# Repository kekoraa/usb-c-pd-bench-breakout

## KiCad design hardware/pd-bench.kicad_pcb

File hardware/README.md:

# KiCad project

Open **pd-bench.kicad_pro** in KiCad 10.0.x. Revision 0.2 contains a fully routed PCB, checked with KiCad CLI 10.0.5. Keep this folder and its local libraries together.

```text
hardware/
  pd-bench.kicad_pro       Project settings and net classes
  pd-bench.kicad_sch       One-sheet A3 schematic (electrically unchanged)
  pd-bench.kicad_pcb       Routed 80 x 70 mm two-layer PCB
  pd-bench.kicad_dru       Documented J1-specific design rules
  sym-lib-table           Project-relative symbol library
  fp-lib-table            Project-relative footprint library
  libraries/
    PD_Bench.kicad_sym
    PD_Bench.pretty/
```

The PCB contains 27 schematic-linked footprints and four board-only mounting holes, 112 track segments, 48 vias and three filled copper zones. There are zero unconnected items under the supplied DRC. Four additional zones are mounting-hardware keepout areas, not copper pours.

Local symbols and footprints are derived from KiCad standard libraries. The MOSFET symbol represents G1/D2/S3. J3/J4 nominal drills have been changed to 1.1 mm in both board and local libraries. The USB footprint retains the manufacturer's land pattern and uses a documented 0.19 mm internal hole-clearance rule. Fabricator acceptance of its nominal 0.1944 mm spacing remains open.

Optional component 3D bodies reference KiCad's standard model library. The supplied bare-board CAD render intentionally does not establish an assembled hardware result. Use the copper exports and native PCB to inspect routing.

Before fabrication, review the [layout](../docs/pcb-layout.md), [routing assessment](../docs/routing-review.md) and [open issues](../docs/open-issues.md). This is an unbuilt design prototype; no manufacturing files are released.

Re-run from the repository root with `kicad-cli` on the path:

```sh
kicad-cli sch erc -o verification/erc.rpt hardware/pd-bench.kicad_sch
kicad-cli sch export netlist --format kicadxml -o verification/netlist.xml hardware/pd-bench.kicad_sch
kicad-cli pcb drc --refill-zones --save-board --schematic-parity --exit-code-violations -o verification/drc.rpt hardware/pd-bench.kicad_pcb
python verification/check_connectivity.py
```

The optional `verification/inspect_routed_board.py` uses KiCad's bundled Python/pcbnew module to compare every PCB pin with the exported schematic and report routing/zone statistics. File checks are not electrical simulation or physical validation.

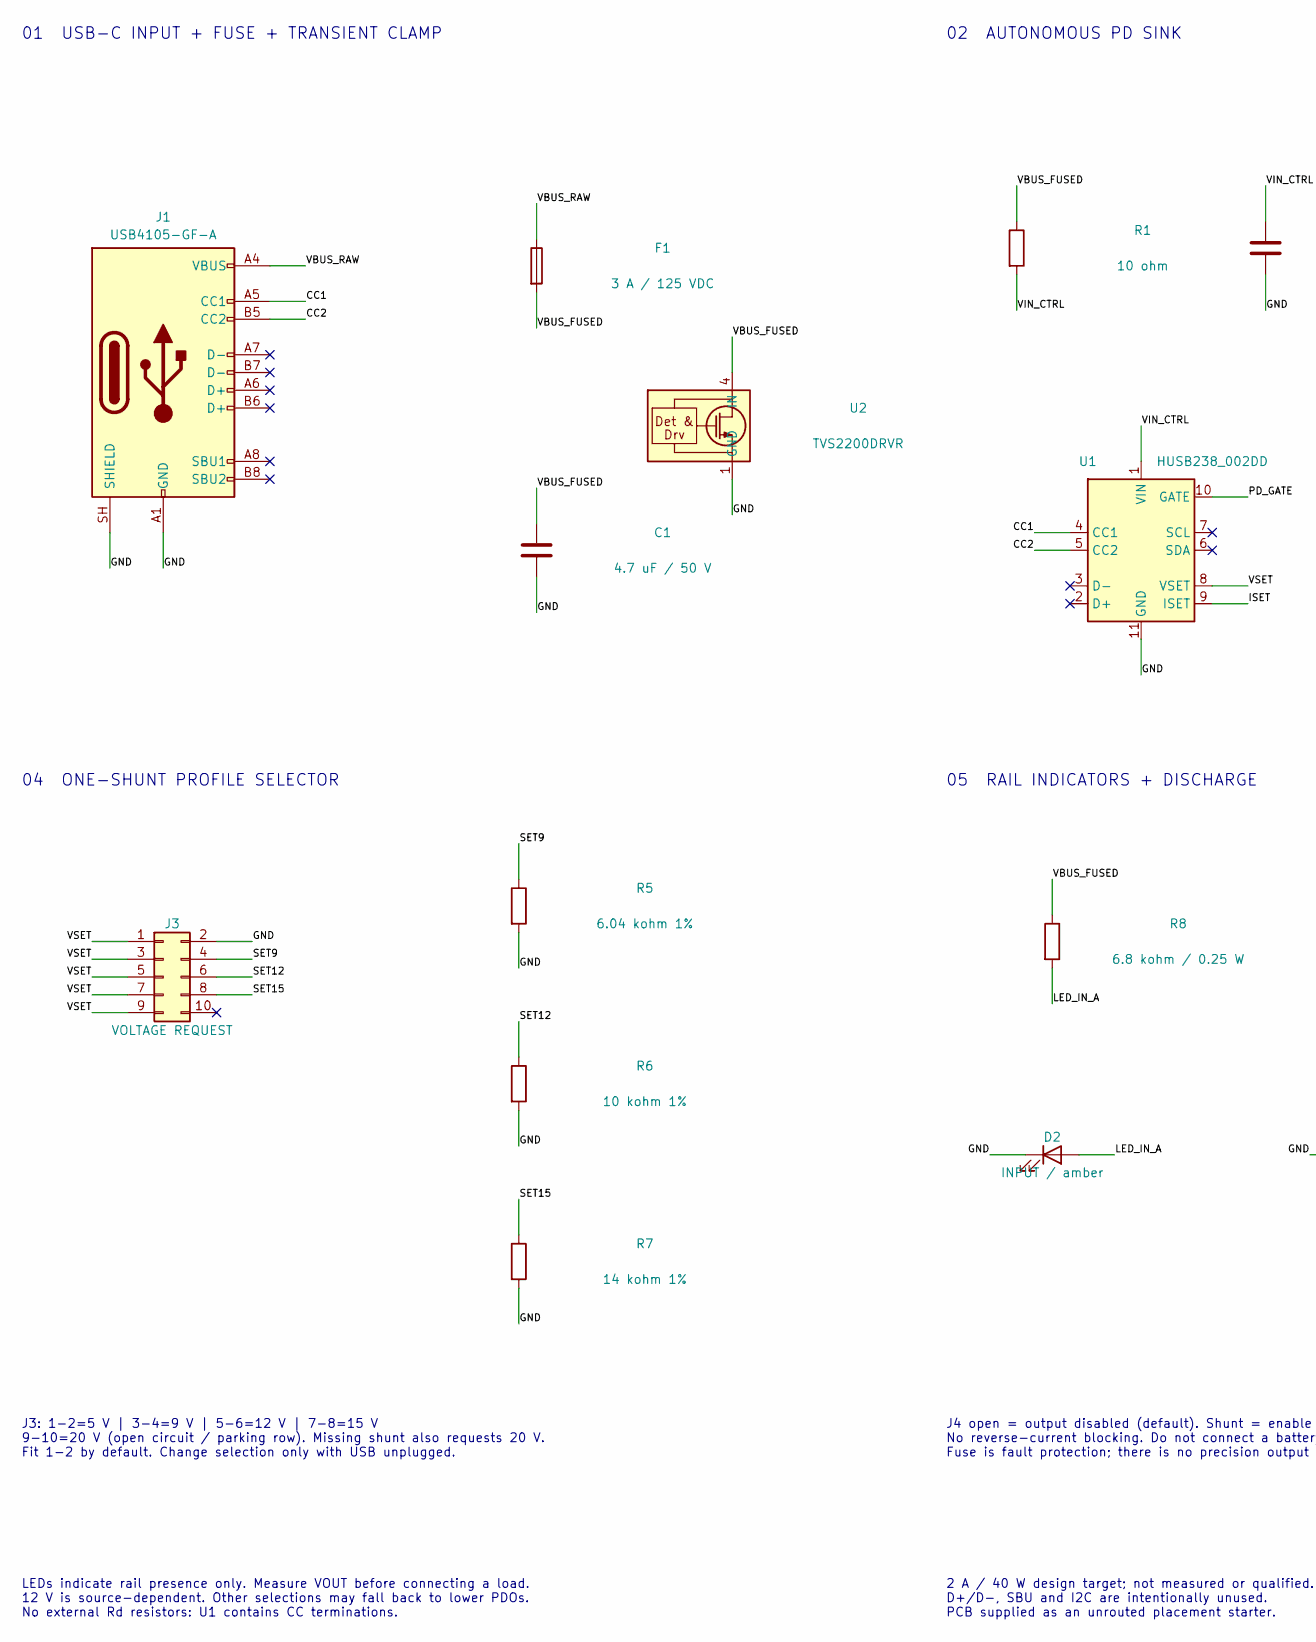
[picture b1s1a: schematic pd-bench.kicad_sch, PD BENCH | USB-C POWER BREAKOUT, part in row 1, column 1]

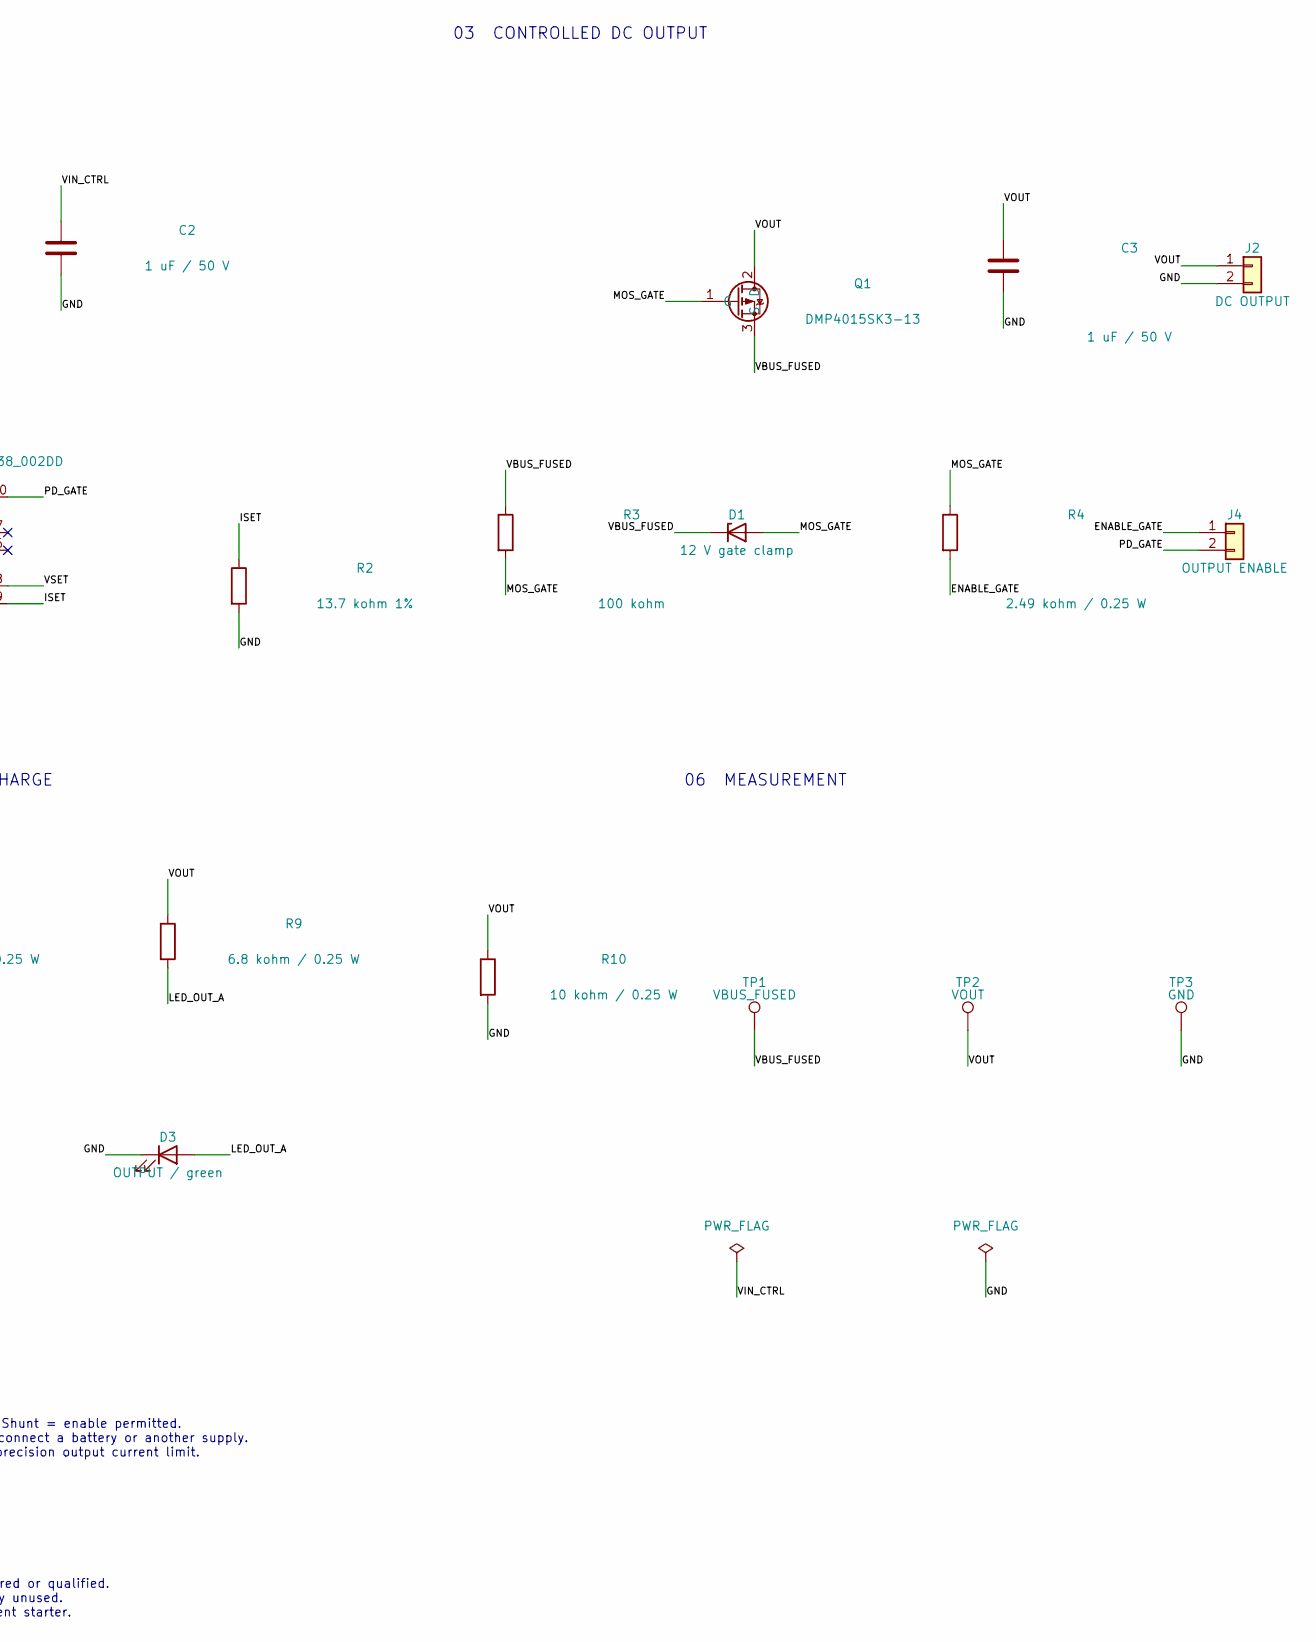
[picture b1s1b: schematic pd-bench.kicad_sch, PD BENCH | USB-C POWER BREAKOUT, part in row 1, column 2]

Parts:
C1: 4.7 uF / 50 V; C_1206_3216Metric; MPN GRM31CR71H475KA12L
C2, C3: 1 uF / 50 V; C_0805_2012Metric; MPN C2012X7R1H105K125AB
D1: 12 V gate clamp; D_SOD-123; MPN BZT52-C12X
D2: INPUT / amber; LED_0805_2012Metric; MPN LTST-C170KSKT
D3: OUTPUT / green; LED_0805_2012Metric; MPN LTST-C170KGKT
F1: 3 A / 125 VDC; Fuse_Littelfuse-NANO2-451_453; MPN 0451003.MRL
J1: USB4105-GF-A; USB_C_Receptacle_GCT_USB4105-xx-A_16P_TopMnt_Horizontal; MPN USB4105-GF-A
J2: DC OUTPUT; TerminalBlock_Phoenix_MKDS-1,5-2_1x02_P5.00mm_Horizontal; MPN 1715022
J3: VOLTAGE REQUEST; PinHeader_2x05_P2.54mm_Vertical; MPN 61301021121
J4: OUTPUT ENABLE; PinHeader_1x02_P2.54mm_Vertical; MPN 61300211121
Q1: DMP4015SK3-13; TO-252-2; MPN DMP4015SK3-13
R1: 10 ohm; R_0805_2012Metric; MPN RC0805FR-0710RL
R2: 13.7 kohm 1%; R_0805_2012Metric; MPN RC0805FR-0713K7L
R3: 100 kohm; R_0805_2012Metric; MPN RC0805FR-07100KL
R4: 2.49 kohm / 0.25 W; R_1206_3216Metric; MPN RC1206FR-072K49L
R5: 6.04 kohm 1%; R_0805_2012Metric; MPN RC0805FR-076K04L
R6: 10 kohm 1%; R_0805_2012Metric; MPN RC0805FR-0710KL
R7: 14 kohm 1%; R_0805_2012Metric; MPN RC0805FR-0714KL
R8, R9: 6.8 kohm / 0.25 W; R_1206_3216Metric; MPN RC1206FR-076K8L
R10: 10 kohm / 0.25 W; R_1206_3216Metric; MPN RC1206FR-0710KL
TP1: VBUS_FUSED; TestPoint_Pad_D2.0mm; MPN PCB pad
TP2: VOUT; TestPoint_Pad_D2.0mm; MPN PCB pad
TP3: GND; TestPoint_Pad_D2.0mm; MPN PCB pad
U1: HUSB238_002DD; WDFN-10-1EP_3x3mm_P0.5mm_EP1.8x2.5mm; MPN HUSB238_002DD
U2: TVS2200DRVR; WSON-6-1EP_2x2mm_P0.65mm_EP1x1.6mm; MPN TVS2200DRVR

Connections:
/CC1: J1.A5 (CC1), U1.4 (CC1)
/CC2: J1.B5 (CC2), U1.5 (CC2)
/ENABLE_GATE: J4.1, R4.2
/GND: C1.2, C2.2, C3.2, D2.1 (K), D3.1 (K), J1.A1 (GND), J1.A12 (GND), J1.B1 (GND), J1.B12 (GND), J1.SH (SHIELD), J2.2, J3.2, R2.2, R5.2, R6.2, R7.2, R10.2, TP3.1, U1.11 (GND), U2.1 (GND), U2.2 (GND), U2.3 (GND), U2.7 (GND)
/ISET: R2.1, U1.9 (ISET)
/LED_IN_A: D2.2 (A), R8.2
/LED_OUT_A: D3.2 (A), R9.2
/MOS_GATE: D1.2 (A), Q1.1 (G), R3.2, R4.1
/PD_GATE: J4.2, U1.10 (GATE)
/SET9: J3.4, R5.1
/SET12: J3.6, R6.1
/SET15: J3.8, R7.1
/VBUS_FUSED: C1.1, D1.1 (K), F1.2, Q1.3 (S), R1.1, R3.1, R8.1, TP1.1, U2.4 (IN), U2.5 (IN), U2.6 (IN)
/VBUS_RAW: F1.1, J1.A4 (VBUS), J1.A9 (VBUS), J1.B4 (VBUS), J1.B9 (VBUS)
/VIN_CTRL: C2.1, R1.2, U1.1 (VIN)
/VOUT: C3.1, J2.1, Q1.2 (D), R9.1, R10.1, TP2.1
/VSET: J3.1, J3.3, J3.5, J3.7, J3.9, U1.8 (VSET)

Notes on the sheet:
01 USB-C INPUT + FUSE + TRANSIENT CLAMP
02 AUTONOMOUS PD SINK
03 CONTROLLED DC OUTPUT
04 ONE-SHUNT PROFILE SELECTOR
05 RAIL INDICATORS + DISCHARGE
06 MEASUREMENT
J3: 1-2=5 V | 3-4=9 V | 5-6=12 V | 7-8=15 V 9-10=20 V (open circuit / parking row). Missing shunt also requests 20 V. Fit 1-2 by default. Change selection only with USB unplugged.
J4 open = output disabled (default). Shunt = enable permitted. No reverse-current blocking. Do not connect a battery or another supply. Fuse is fault protection; there is no precision output current limit.
LEDs indicate rail presence only. Measure VOUT before connecting a load. 12 V is source-dependent. Other selections may fall back to lower PDOs. No external Rd resistors: U1 contains CC terminations.
2 A / 40 W design target; not measured or qualified. D+/D-, SBU and I2C are intentionally unused. PCB supplied as an unrouted placement starter.

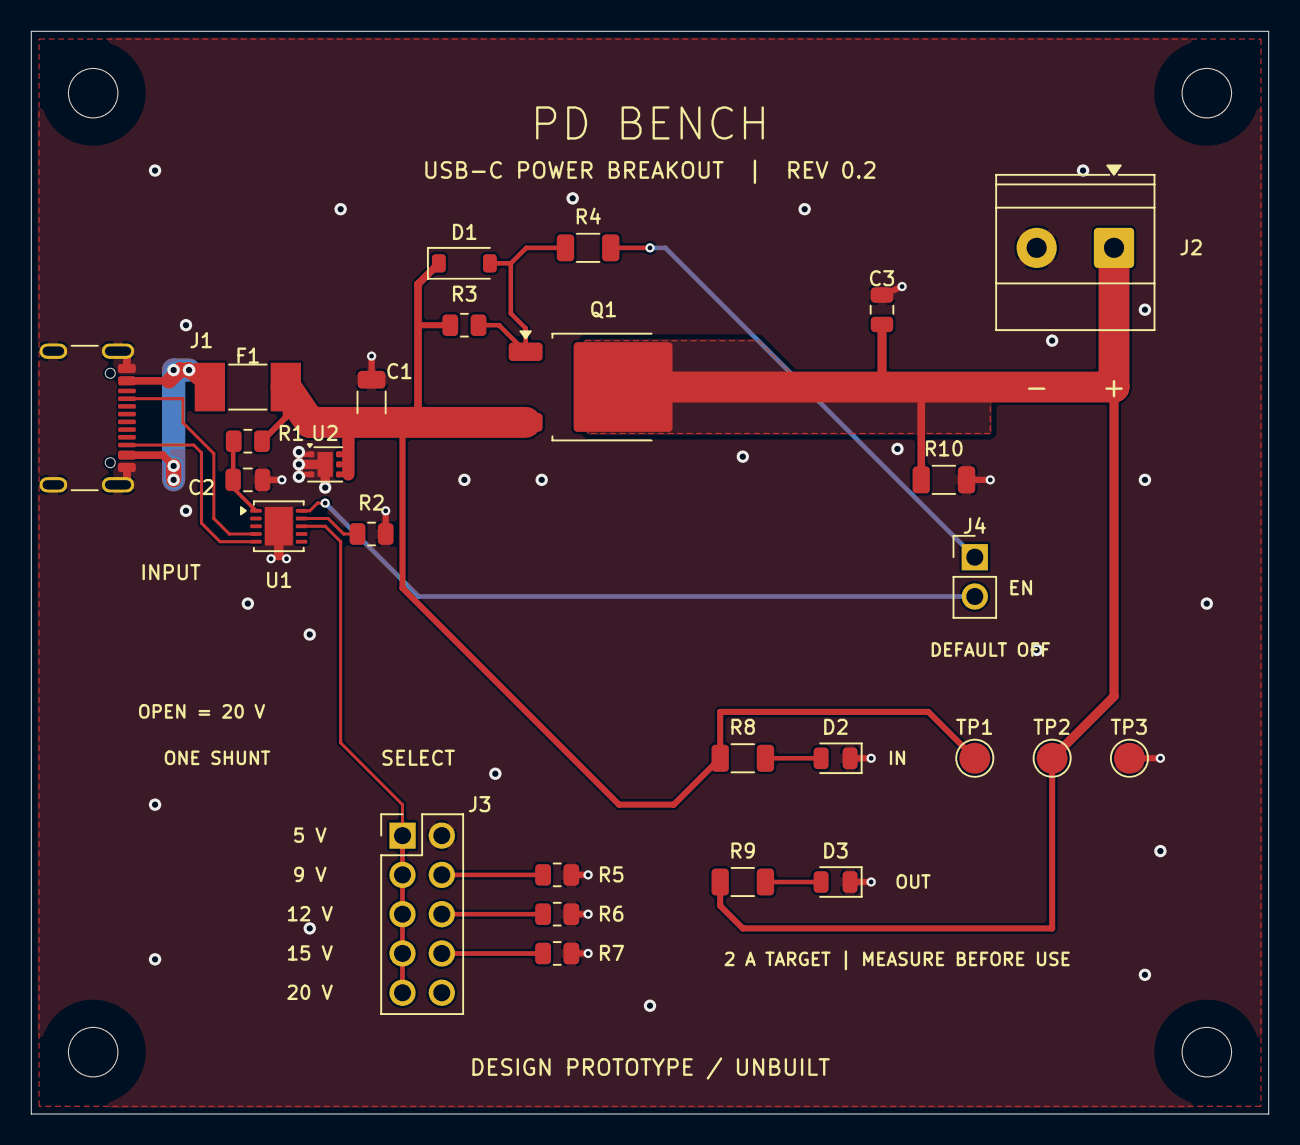
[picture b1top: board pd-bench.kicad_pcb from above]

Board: 2 copper layers, 80.0 x 70.0 mm, 31 parts (0 on the bottom side), 17 nets.

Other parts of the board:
H1, H2, H3, H4: M3; MountingHole_3.2mm_M3
